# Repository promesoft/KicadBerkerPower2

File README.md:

# KicadBerkerPower2
Black board

# Mix project
The board consists of 5 separate sections that can be separated. On the backside its easy to see the different ground planes and where to cut the board if needed.

## Status - Rev A Produced 3 of 5 sections working
### Errata
 * Copper goes under ESP12E modules - thereby eliminating the Wifi antenna...
 
### Issues and Notes
 - The two ESP12 modules are difficult to program

 - The Wemos D1 mini section should not be used for 230V but works nevertheless.

 - The rest is fine.

## Physical Construction

## Features

# Details
## Wemos D1 mini - section 1
Section 1 is the largest section on the board. It is intended as a development board for section 2 and 3.
Section 1 has an AM2320, a relay and a power supply. Besides this it has breakout of several pins and an LED for debug/information.
### Issues
There is one flaw with section 1 that should be addressed: The pins on the power connector are too close for 230V operation as the centerpin of the relay bridges the live and neutral (calculated to be min 2,3mm between open terminals - 3,2mm for certification) 

### I2S connector 
D1 - SCL

D2 - SDA
### AM2320 
D1 - SCL

D2 - SDA
### Relay
D3 - Active high
### HLK-PM03 PSU
+3v PSU supply if mounted 
Connector not suitable for 230V
Protection: Varistor
External Fuse needed
### Pull down LED
D8 - active low
## ESP12S - Section 2
Section 2 is the smaller than section 1 but with most features of it.
### AM2320 
### Relay
### HLK-PM03 PSU
## ESP12S - Section 3
No reset or programming assistance (pulldn/up etc)
Programming via Rx/Tx (or preprogrammed)
### AM2320 
### Relay
### HLK-PM03 PSU
## PSU - Virtual GDN - "Floating ground section"
Sometimes you only have a single ended supply but need a positive and negative supply.
This little board provides a low power balanced center that can be used as GND. So a +24 V single ended supply becomes a +/-12V supply.

### Input +/- supply
eg +24Vin and a "GNDin"
### Output + 0 - supply
becomes a +12V (same as +24in) GND and -12V (same as GNDin)
### Output regulated +5v GND (78L05)
The +12Vout is fed to a low power regulator for 5V output
## PSU
### Input + 0 - supply
### Output + 0 - regulated supply (78xx and 79xx)

#Cutout

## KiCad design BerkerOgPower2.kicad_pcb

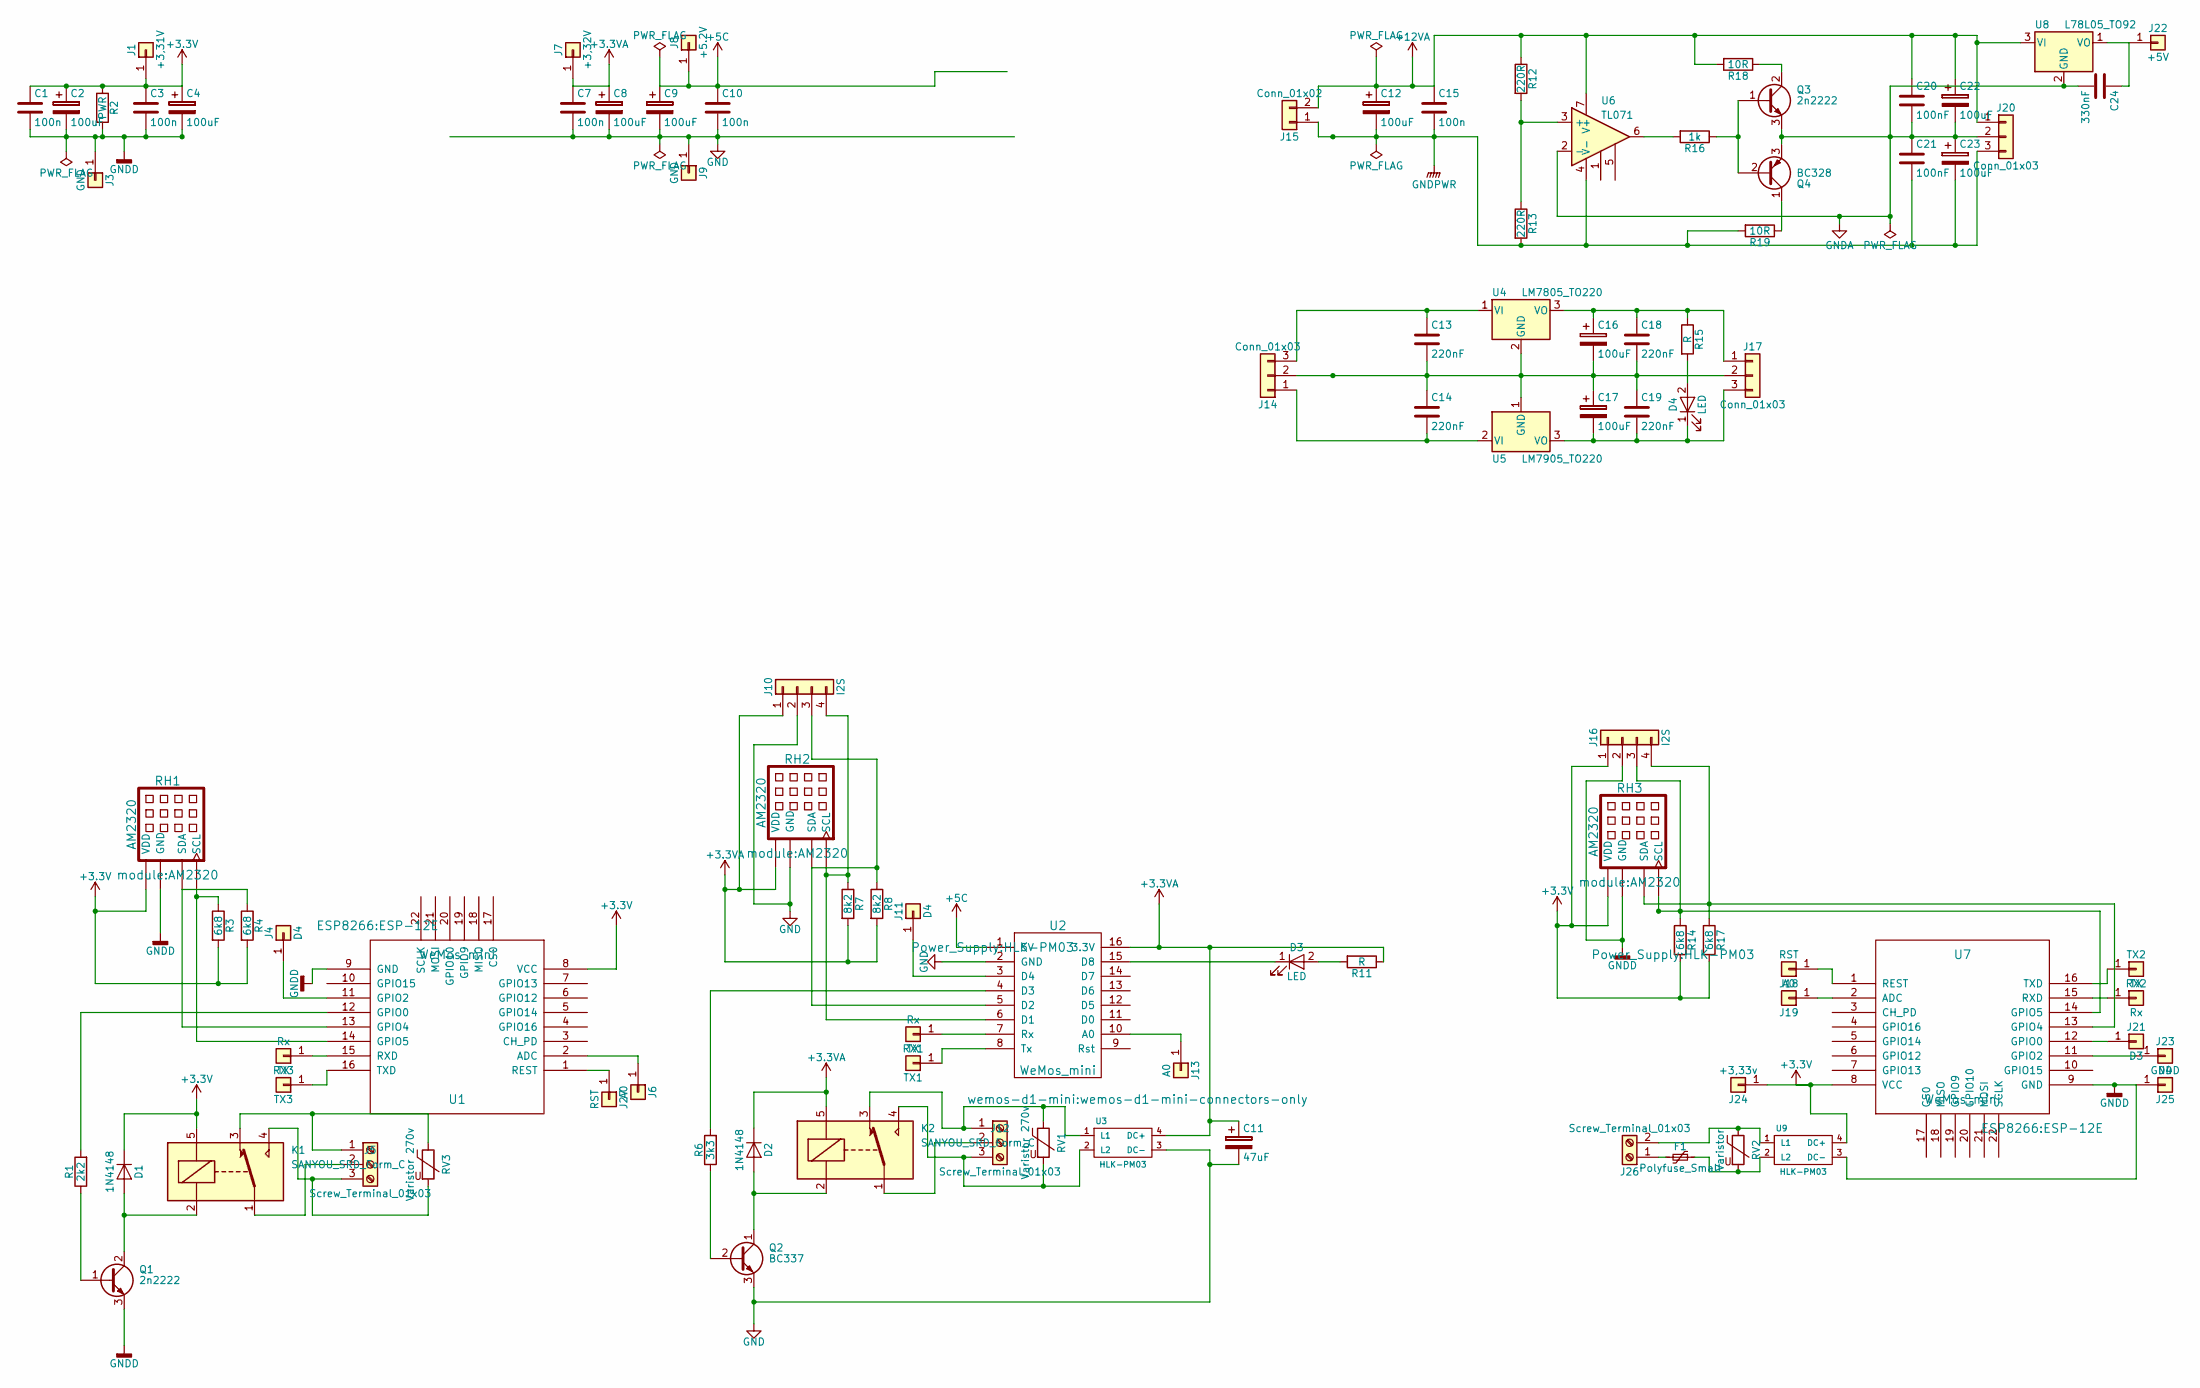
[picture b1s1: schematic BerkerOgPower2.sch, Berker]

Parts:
C1, C3, C7, C10, C15: 100n; C_0805_HandSoldering
C2, C4, C8, C9, C12: 100uF; CP_Tantalum_Case-C_EIA-6032-28_Hand
C11: 47uF; CP_Radial_D5.0mm_P2.50mm
C13, C14, C18, C19: 220nF; C_Disc_D10.0mm_W2.5mm_P5.00mm
C16, C17, C22, C23: 100uF; CP_Radial_D10.0mm_P3.80mm
C20, C21: 100nF; C_1206_HandSoldering
C24: 330nF; C_1206_HandSoldering
D1, D2: 1N4148; D_DO-35_SOD27_P7.62mm_Horizontal
D3, D4: LED; LED_D3.0mm
F1: Polyfuse_Small; R_2512_HandSoldering
J1: +3,31V; Socket_Strip_Straight_1x01_Pitch2.54mm
J3, J9: GND; Socket_Strip_Straight_1x01_Pitch2.54mm
J4, J11, J23: D4; Socket_Strip_Straight_1x01_Pitch2.54mm
J5: Screw_Terminal_01x03; WAGO_734_3pin_Straight_RuggedPads
J6, J13, J19: A0; Socket_Strip_Straight_1x01_Pitch2.54mm
J7: +3,32V; Socket_Strip_Straight_1x01_Pitch2.54mm
J8: +5.2V; Socket_Strip_Straight_1x01_Pitch2.54mm
J10, J16: I2S; Pin_Header_Straight_1x04_Pitch2.54mm
J12: Screw_Terminal_01x03; TerminalBlock_Phoenix_MPT-2.54mm_3pol
J14, J17, J20: Conn_01x03; Pin_Header_Straight_1x03_Pitch2.54mm
J15: Conn_01x02; Pin_Header_Straight_1x02_Pitch2.54mm
J18, J27: RST; Socket_Strip_Straight_1x01_Pitch2.54mm
J21: D3; Socket_Strip_Straight_1x01_Pitch2.54mm
J22: +5V; Socket_Strip_Straight_1x01_Pitch2.54mm
J24: +3,33v; Socket_Strip_Straight_1x01_Pitch2.54mm
J25: GNDD; Socket_Strip_Straight_1x01_Pitch2.54mm
J26: Screw_Terminal_01x03; TerminalBlock_Phoenix_MKDS1.5-2pol
K1, K2: SANYOU_SRD_Form_C; Relay_SPDT_SANYOU_SRD_Series_Form_C
Q1, Q3: 2n2222; SOT-23
Q2: BC337; TO-92_Molded_Narrow
Q4: BC328; TO-92_Molded_Narrow
R1: 2k2; R_0805_HandSoldering
R2: PWR; Resistor_SMD+THTuniversal_0805to1206_RM10_HandSoldering
R3, R4, R14, R17: 6k8; R_0805_HandSoldering
R6: 3k3; R_0805_HandSoldering
R7, R8: 8k2; R_0805_HandSoldering
R11, R15: R; R_0805_HandSoldering
R12, R13: 220R; R_0805_HandSoldering
R16: 1k; R_0805_HandSoldering
R18, R19: 10R; R_0805_HandSoldering
RH1, RH2, RH3: AM2320
RV1, RV3: Varistor 270v; RV_Disc_D12_W3.9_P7.5
RV2: Varistor; RV_Disc_D12_W3.9_P7.5
RX1, RX2, RX3: Rx; Socket_Strip_Straight_1x01_Pitch2.54mm
TX1, TX2, TX3: TX; Socket_Strip_Straight_1x01_Pitch2.54mm
U1, U7: WeMos_mini; ESP-12E
U2: WeMos_mini; wemos-d1-mini-connectors-only
U3, U9: HLK-PM03
U4: LM7805_TO220; TO-220
U5: LM7905_TO220; TO-220
U6: TL071; DIP-8_W7.62mm
U8: L78L05_TO92; TO-92_Inline_Narrow_Oval

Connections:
+3.3VA: C7.1, C8.1, C11.1, D2.1 (K), J7.1, J10.1, K2.5, R7.2, R8.2, R11.1, RH2.1 (VDD), U2.16 (3.3V), U3.4 (DC+)
+3V3: C1.1, C2.1, C3.1, C4.1, D1.1 (K), J1.1, J16.1, J24.1, K1.5, R2.1, R3.2, R4.2, R14.2, R17.2, RH1.1 (VDD), RH3.1 (VDD), U1.8 (VCC), U7.8 (VCC), U9.4 (DC+)
+5C: C9.1, C10.1, J8.1, U2.1 (5V)
+12VA: C12.1, C15.1, C20.1, C22.1, J15.2, J20.1, R12.1, R18.2, U6.7 (V+), U8.3 (VI)
GND: C7.2, C8.2, C9.2, C10.2, C11.2, J9.1, J10.2, Q2.3 (E), RH2.3 (GND), U2.2 (GND), U3.3 (DC-)
GNDA: C20.2, C21.1, C22.2, C23.1, C24.2, J20.2, Q3.3 (E), Q4.3 (E), U6.2 (-), U8.2 (GND)
GNDD: C1.2, C2.2, C3.2, C4.2, J3.1, J16.2, J25.1, Q1.3 (E), R2.2, RH1.3 (GND), RH3.3 (GND), U1.9 (GND), U7.9 (GND), U9.3 (DC-)
GNDPWR: C12.2, C15.2, C21.2, C23.2, J15.1, J20.3, R13.2, R19.2, U6.4 (V-)
unnamed: C13.1, J14.3, U4.1 (VI)
unnamed: C13.2, C14.1, C16.2, C17.1, C18.2, C19.1, J14.2, J17.2, U4.2 (GND), U5.1 (GND)
unnamed: C14.2, J14.1, U5.2 (VI)
unnamed: C16.1, C18.1, J17.1, R15.1, U4.3 (VO)
unnamed: C17.2, C19.2, D4.1 (K), J17.3, U5.3 (VO)
unnamed: C24.1, J22.1, U8.1 (VO)
unnamed: D1.2 (A), K1.2, Q1.2 (C)
unnamed: D2.2 (A), K2.2, Q2.1 (C)
unnamed: D3.1 (K), U2.15 (D8)
unnamed: D3.2 (A), R11.2
unnamed: D4.2 (A), R15.2
unnamed: F1.1, RV2.2, U9.2 (L2)
unnamed: F1.2, J26.1
unnamed: J4.1, U1.11 (GPIO2)
unnamed: J5.1, K1.3, RV3.1
unnamed: J5.2, K1.1
unnamed: J5.3, K1.4, RV3.2
unnamed: J6.1, U1.2 (ADC)
unnamed: J10.3, R8.1, RH2.2 (SDA), U2.5 (D2)
unnamed: J10.4, R7.1, RH2.4 (SCL), U2.6 (D1)
unnamed: J11.1, U2.3 (D4)
unnamed: J12.1, K2.3, RV1.1, U3.1 (L1)
unnamed: J12.2, K2.1
unnamed: J12.3, K2.4, RV1.2, U3.2 (L2)
unnamed: J13.1, U2.10 (A0)
unnamed: J16.3, R14.1, RH3.4 (SCL), U7.14 (GPIO5)
unnamed: J16.4, R17.1, RH3.2 (SDA), U7.13 (GPIO4)
unnamed: J18.1, U7.1 (REST)
unnamed: J19.1, U7.2 (ADC)
unnamed: J21.1, U7.12 (GPIO0)
unnamed: J23.1, U7.11 (GPIO2)
unnamed: J26.2, RV2.1, U9.1 (L1)
unnamed: J27.1, U1.1 (REST)
unnamed: Q1.1 (B), R1.1
unnamed: Q2.2 (B), R6.1
unnamed: Q3.1 (B), Q4.2 (B), R16.1
unnamed: Q3.2 (C), R18.1
unnamed: Q4.1 (C), R19.1
unnamed: R1.2, U1.12 (GPIO0)
unnamed: R3.1, RH1.4 (SCL), U1.14 (GPIO5)
unnamed: R4.1, RH1.2 (SDA), U1.13 (GPIO4)
unnamed: R6.2, U2.4 (D3)
unnamed: R12.2, R13.1, U6.3 (+)
unnamed: R16.2, U6.6
unnamed: RX1.1, U2.7 (Rx)
unnamed: RX2.1, U7.15 (RXD)
unnamed: RX3.1, U1.15 (RXD)
unnamed: TX1.1, U2.8 (Tx)
unnamed: TX2.1, U7.16 (TXD)
unnamed: TX3.1, U1.16 (TXD)

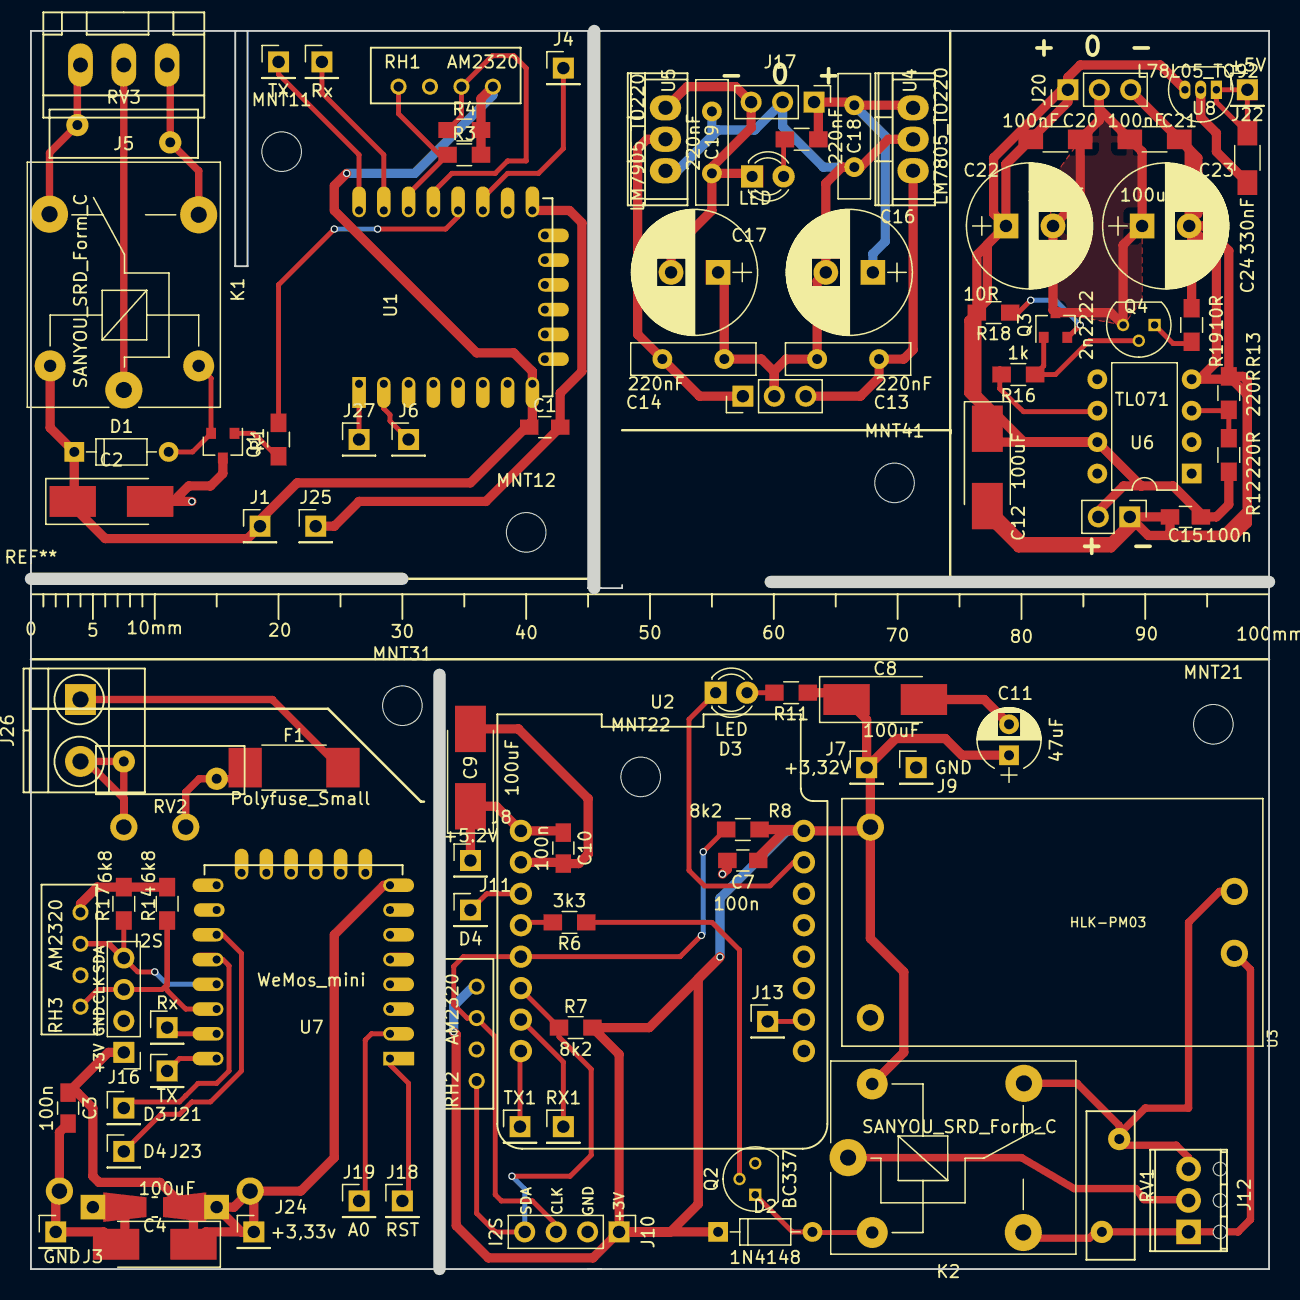
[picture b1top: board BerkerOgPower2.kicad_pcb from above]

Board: 2 copper layers, 100.0 x 100.0 mm, 102 parts (1 on the bottom side), 58 nets.

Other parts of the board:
MNT11, MNT12, MNT21, MNT22, MNT31, MNT41: MountingHole_3.2mm_M3

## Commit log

2018-12-17 Commit after project creation
    Project performed outside Git...
2018-12-17 Pictures
    3D and schematic
2018-12-17 Update README.md
    formatting and text
2018-12-17 Update README.md
    minor
2018-12-17 Update README.md
    Pinout section 1
2018-12-17 rename sch
    sch sect 1
2018-12-18 Update README.md
    3D pict
2018-12-18 Update README.md
    3D
2018-12-19 Update README.md
    cutting text
2018-12-20 Update README.md
    section 1 explained
2018-12-20 Update README.md
    issues
2018-12-25 Update README.md
    cut out
2019-01-15 New 3D
2019-01-15 cleanup folders
2019-01-28 3D updated + Picture
2019-01-28 New 3D models
2019-09-13 Create fp-info-cache
